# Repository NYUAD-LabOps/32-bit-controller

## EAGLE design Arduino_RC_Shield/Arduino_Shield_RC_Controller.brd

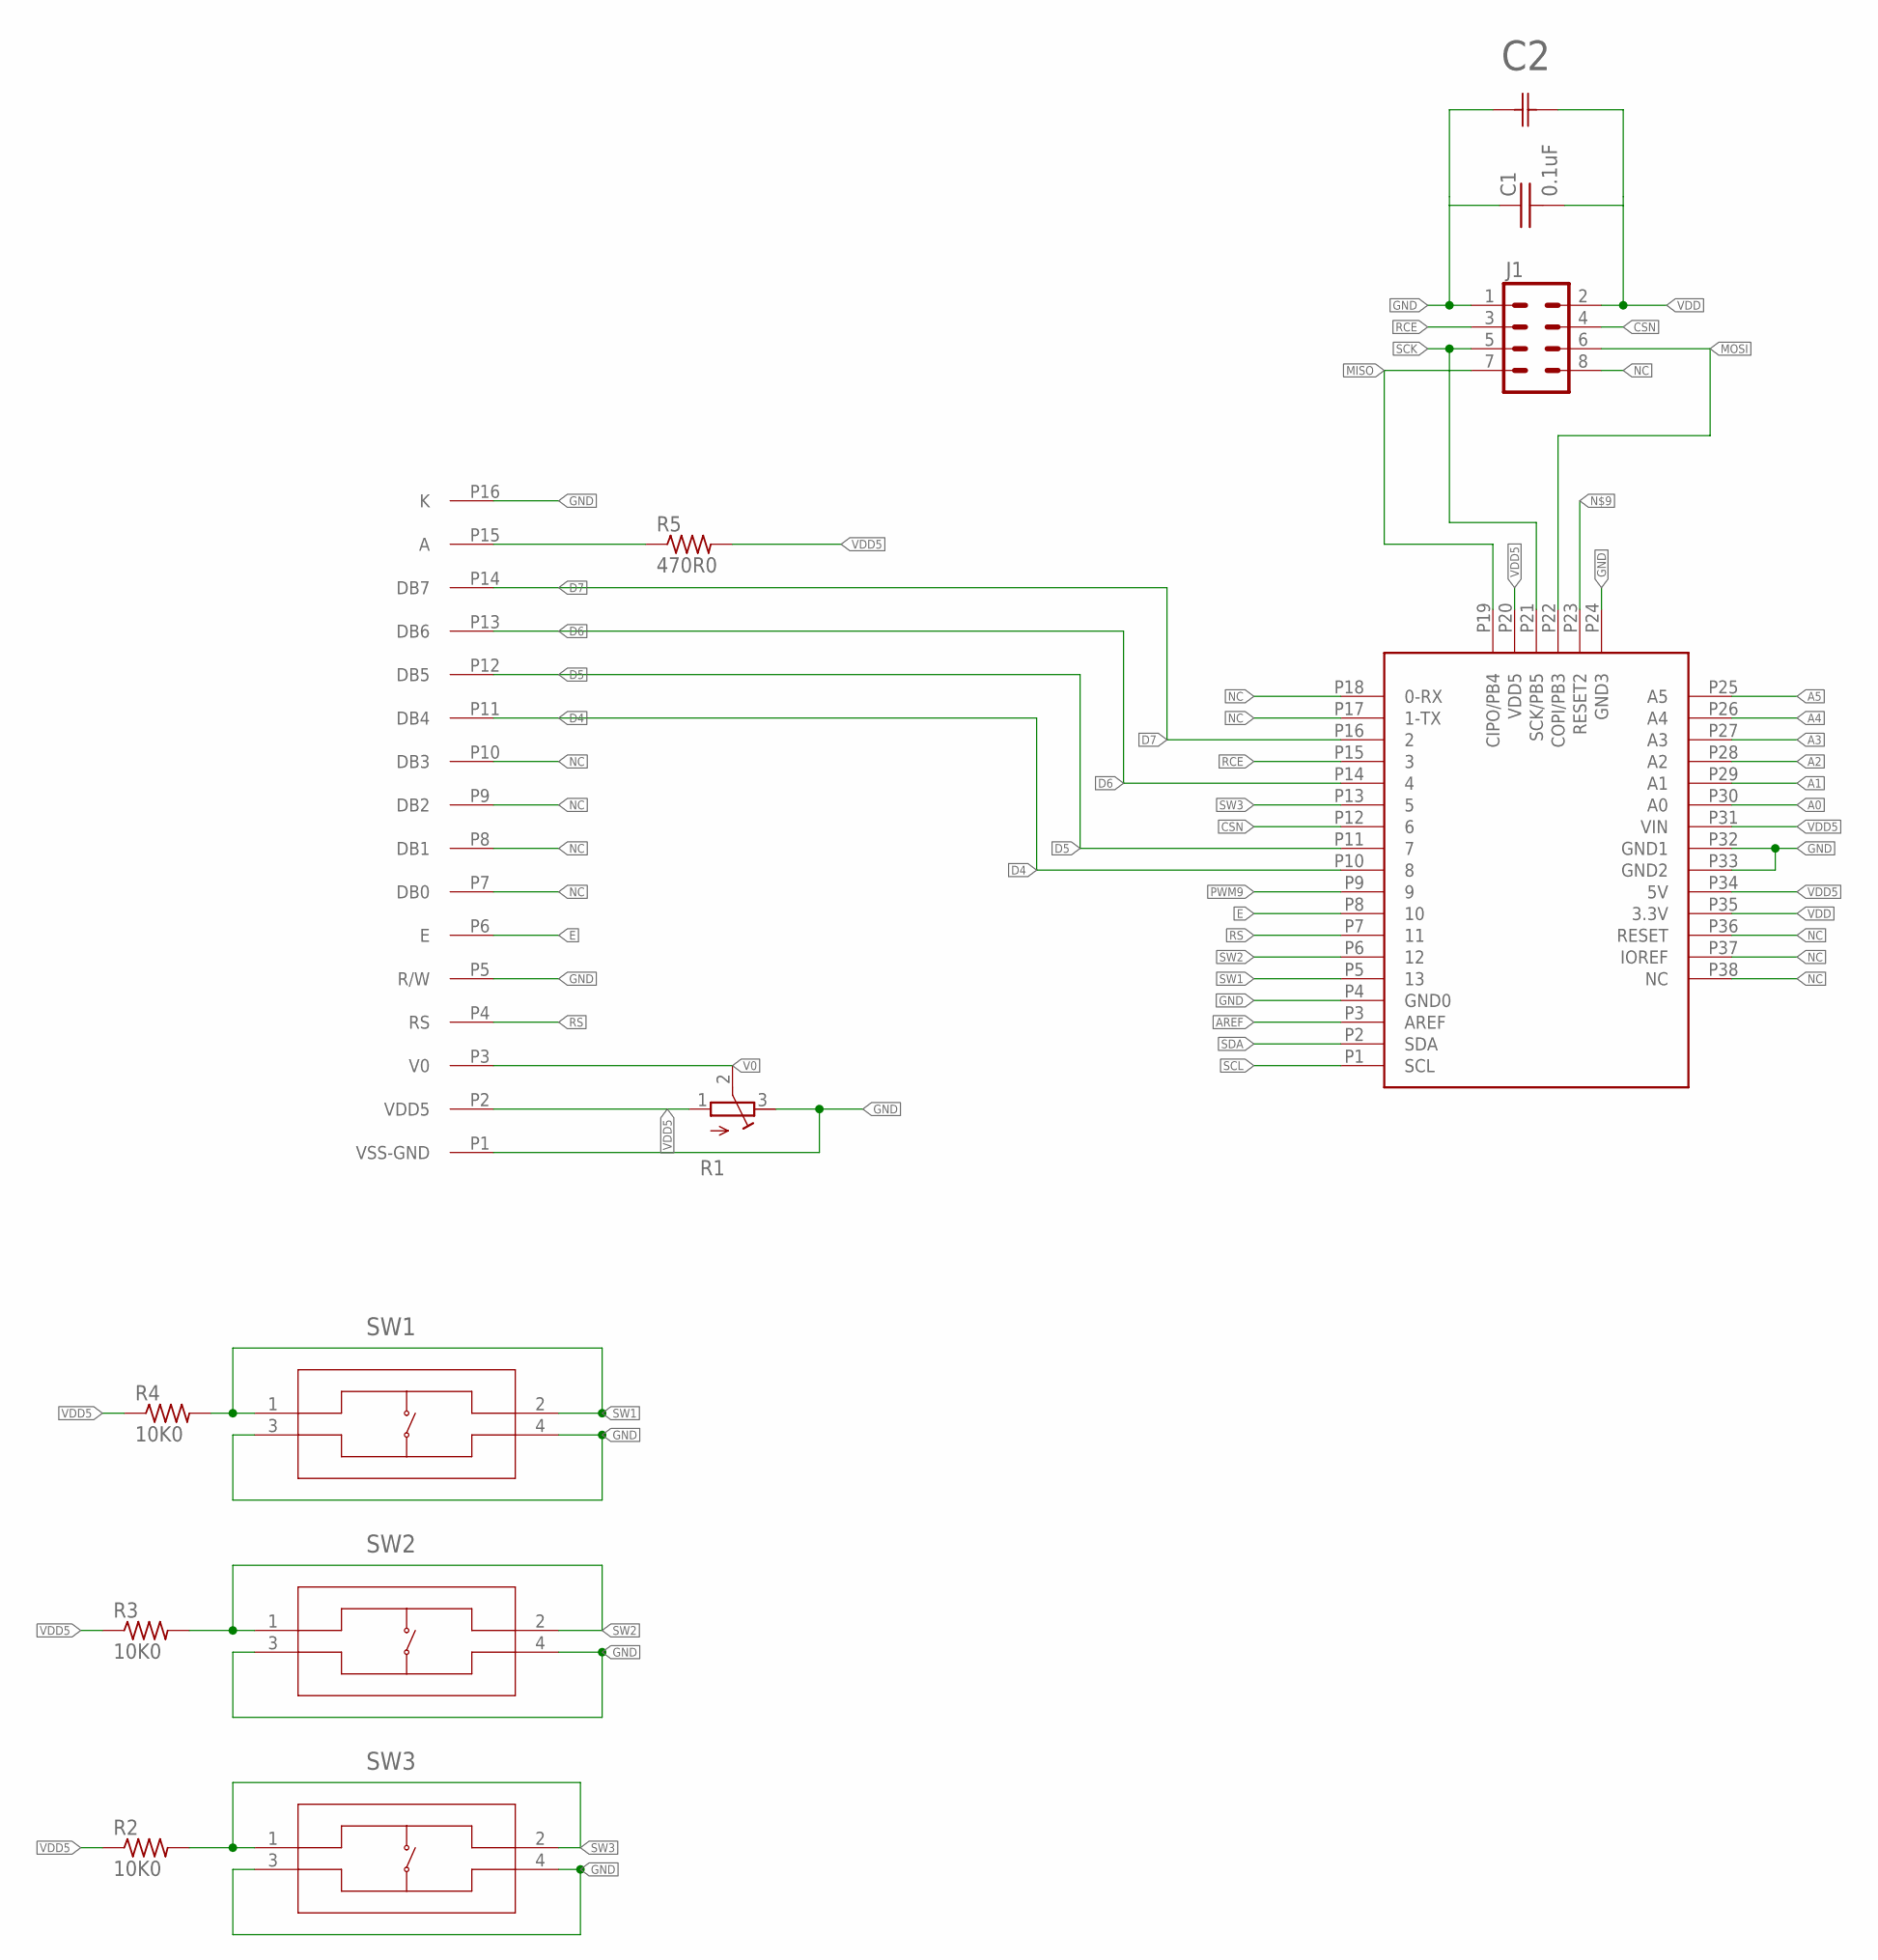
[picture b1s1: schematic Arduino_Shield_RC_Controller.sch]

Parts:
AR1: ARDUINO_R3
C1: 0.1uF; 0402
C2: CAP_470UF_RAD_TH; CAP_YX_10X16_RUB
J1: CONN_04X2; 2X4
LCD1: ADM1602K
R1: R-TRIMM3103; RTRIM3103
R2, R3, R4: 10K0; 0402
R5: 470R0; 0402
SW1, SW2, SW3: PTS810SJG250SMTRLFS; PTS810

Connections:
A0: AR1.P30 (A0)
A1: AR1.P29 (A1)
A2: AR1.P28 (A2)
A3: AR1.P27 (A3)
A4: AR1.P26 (A4)
A5: AR1.P25 (A5)
AREF: AR1.P3 (AREF)
CSN: AR1.P12 (6), J1.4
D4: AR1.P10 (8), LCD1.P11 (DB4)
D5: AR1.P11 (7), LCD1.P12 (DB5)
D6: AR1.P14 (4), LCD1.P13 (DB6)
D7: AR1.P16 (2), LCD1.P14 (DB7)
E: AR1.P8 (10), LCD1.P6 (E)
GND: AR1.P4 (GND0), AR1.P24 (GND3), AR1.P32 (GND1), AR1.P33 (GND2), C1.P$1 (1), C2.1, J1.1, LCD1.P1 (VSS-GND), LCD1.P5 (R/W), LCD1.P16 (K), R1.3 (E), SW1.3, SW1.4, SW2.3, SW2.4, SW3.3, SW3.4
MISO: AR1.P19 (CIPO/PB4), J1.7
MOSI: AR1.P22 (COPI/PB3), J1.6
unnamed: LCD1.P15 (A), R5.P$1 (1)
NC: AR1.P17 (1-TX), AR1.P18 (0-RX), AR1.P36 (RESET), AR1.P37 (IOREF), AR1.P38 (NC), J1.8, LCD1.P7 (DB0), LCD1.P8 (DB1), LCD1.P9 (DB2), LCD1.P10 (DB3)
PWM9: AR1.P9 (9)
RCE: AR1.P15 (3), J1.3
RS: AR1.P7 (11), LCD1.P4 (RS)
SCK: AR1.P21 (SCK/PB5), J1.5
SCL: AR1.P1 (SCL)
SDA: AR1.P2 (SDA)
SW1: AR1.P5 (13), R4.P$2 (2), SW1.1, SW1.2
SW2: AR1.P6 (12), R3.P$2 (2), SW2.1, SW2.2
SW3: AR1.P13 (5), R2.P$2 (2), SW3.1, SW3.2
V0: LCD1.P3 (V0), R1.2 (S)
VDD: AR1.P35 (3.3V), C1.P$2 (2), C2.2, J1.2
VDD5: AR1.P20 (VDD5), AR1.P31 (VIN), AR1.P34 (5V), LCD1.P2 (VDD5), R1.1 (A), R2.P$1 (1), R3.P$1 (1), R4.P$1 (1), R5.P$2 (2)

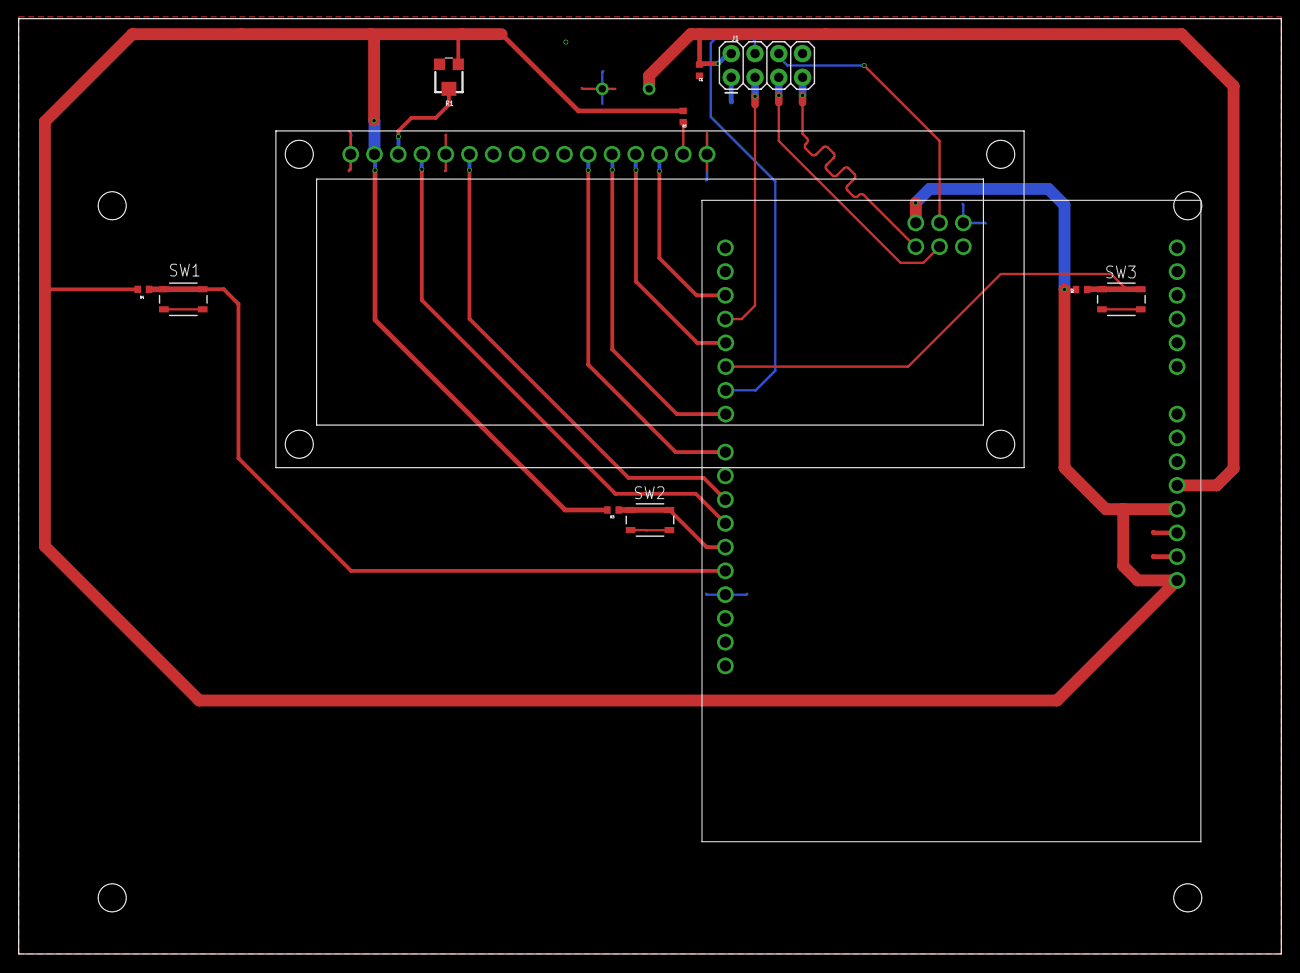
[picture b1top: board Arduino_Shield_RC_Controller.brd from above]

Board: 2 copper layers, 135.0 x 100.0 mm, 13 parts (1 on the bottom side), 20 nets.

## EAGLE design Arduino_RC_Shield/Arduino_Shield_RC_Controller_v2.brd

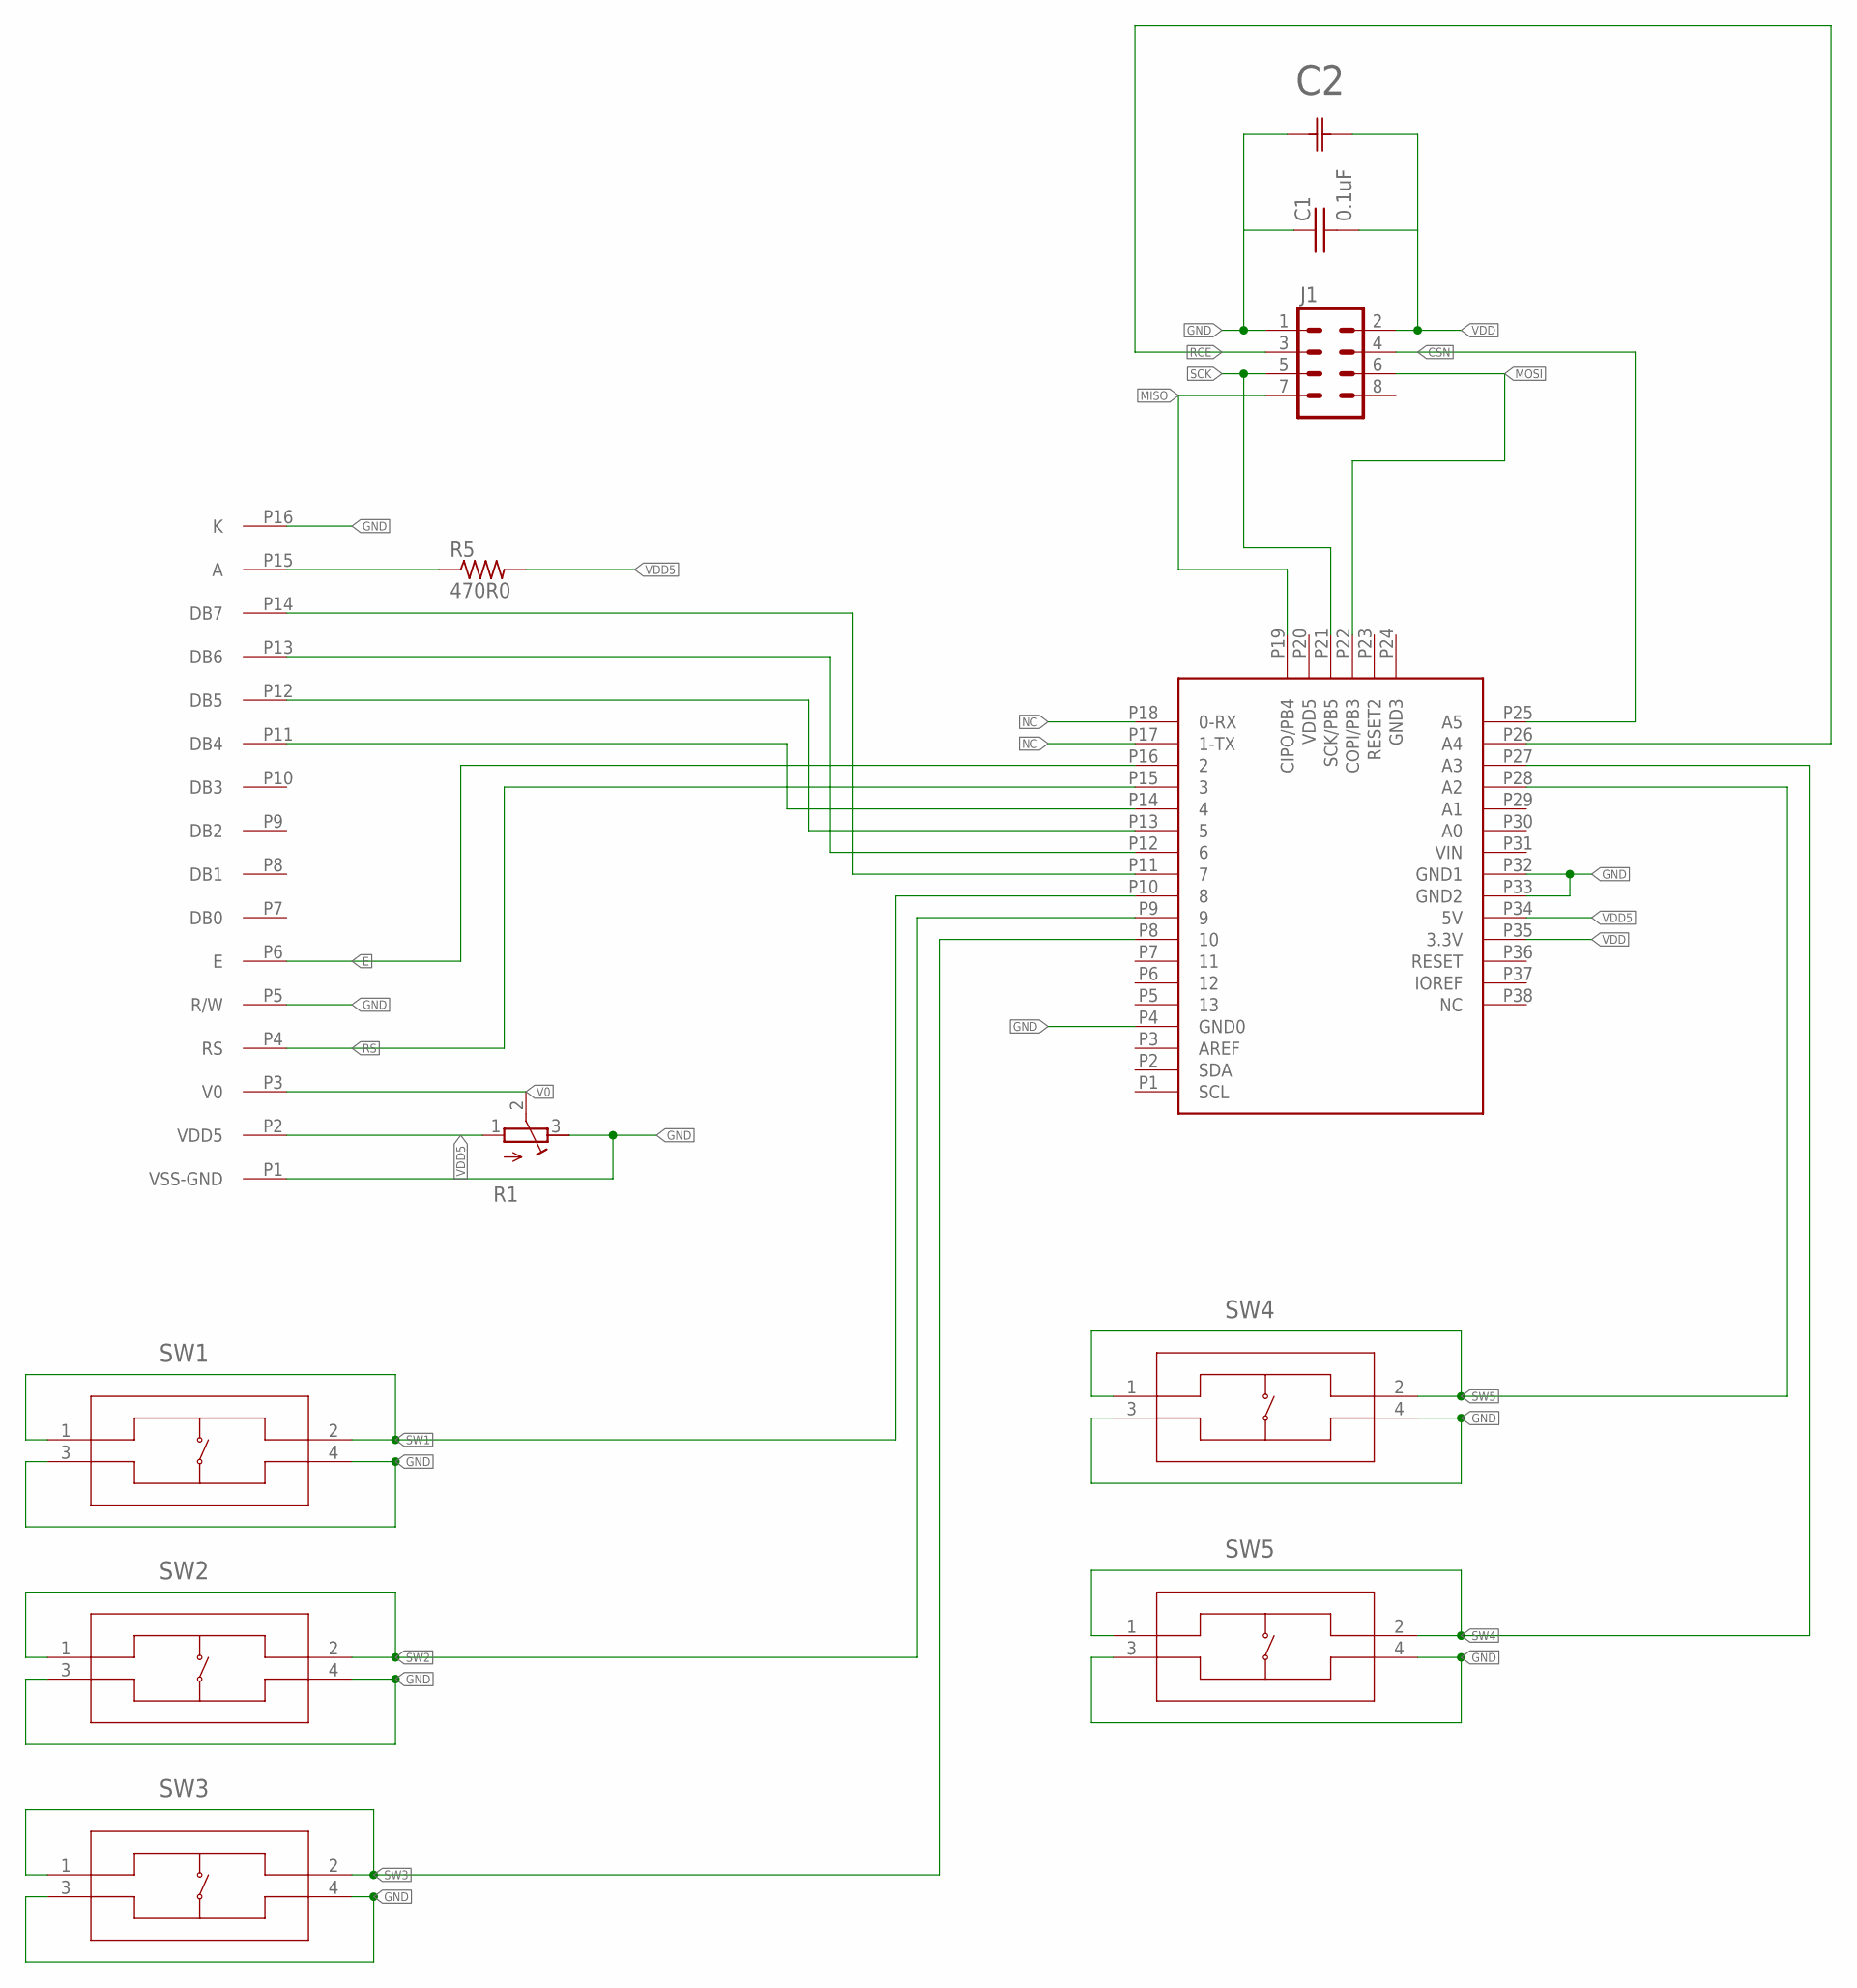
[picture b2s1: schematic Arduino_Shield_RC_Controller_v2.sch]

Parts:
AR1: ARDUINO_R3
C1: 0.1uF; 0402
C2: CAP_470UF_RAD_TH; CAP_YX_10X16_RUB
J1: CONN_04X2; 2X4
LCD1: ADM1602K
R1: R-TRIMM3103; RTRIM3103
R5: 470R0; 0402
SW1, SW2, SW3, SW4, SW5: PTS810SJG250SMTRLFS; PTS810

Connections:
CSN: AR1.P25 (A5), J1.4
E: AR1.P16 (2), LCD1.P6 (E)
GND: AR1.P4 (GND0), AR1.P32 (GND1), AR1.P33 (GND2), C1.P$1 (1), C2.1, J1.1, LCD1.P1 (VSS-GND), LCD1.P5 (R/W), LCD1.P16 (K), R1.3 (E), SW1.3, SW1.4, SW2.3, SW2.4, SW3.3, SW3.4, SW4.3, SW4.4, SW5.3, SW5.4
MISO: AR1.P19 (CIPO/PB4), J1.7
MOSI: AR1.P22 (COPI/PB3), J1.6
unnamed: AR1.P11 (7), LCD1.P14 (DB7)
unnamed: AR1.P12 (6), LCD1.P13 (DB6)
unnamed: AR1.P13 (5), LCD1.P12 (DB5)
unnamed: AR1.P14 (4), LCD1.P11 (DB4)
unnamed: LCD1.P15 (A), R5.P$1 (1)
NC: AR1.P17 (1-TX), AR1.P18 (0-RX)
RCE: AR1.P26 (A4), J1.3
RS: AR1.P15 (3), LCD1.P4 (RS)
SCK: AR1.P21 (SCK/PB5), J1.5
SW1: AR1.P10 (8), SW1.1, SW1.2
SW2: AR1.P9 (9), SW2.1, SW2.2
SW3: AR1.P8 (10), SW3.1, SW3.2
SW4: AR1.P27 (A3), SW5.1, SW5.2
SW5: AR1.P28 (A2), SW4.1, SW4.2
V0: LCD1.P3 (V0), R1.2 (S)
VDD: AR1.P35 (3.3V), C1.P$2 (2), C2.2, J1.2
VDD5: AR1.P34 (5V), LCD1.P2 (VDD5), R1.1 (A), R5.P$2 (2)

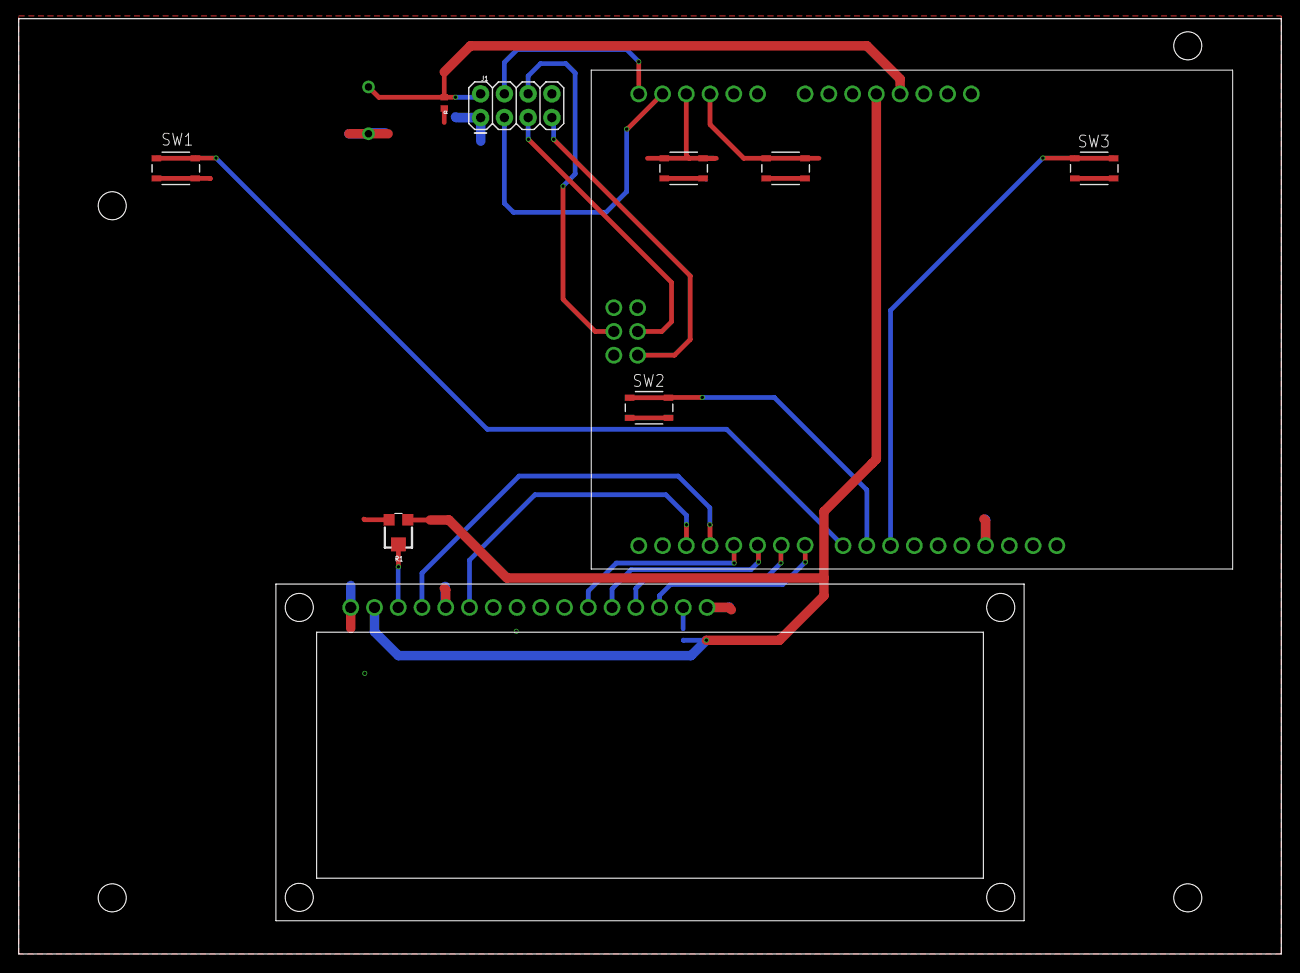
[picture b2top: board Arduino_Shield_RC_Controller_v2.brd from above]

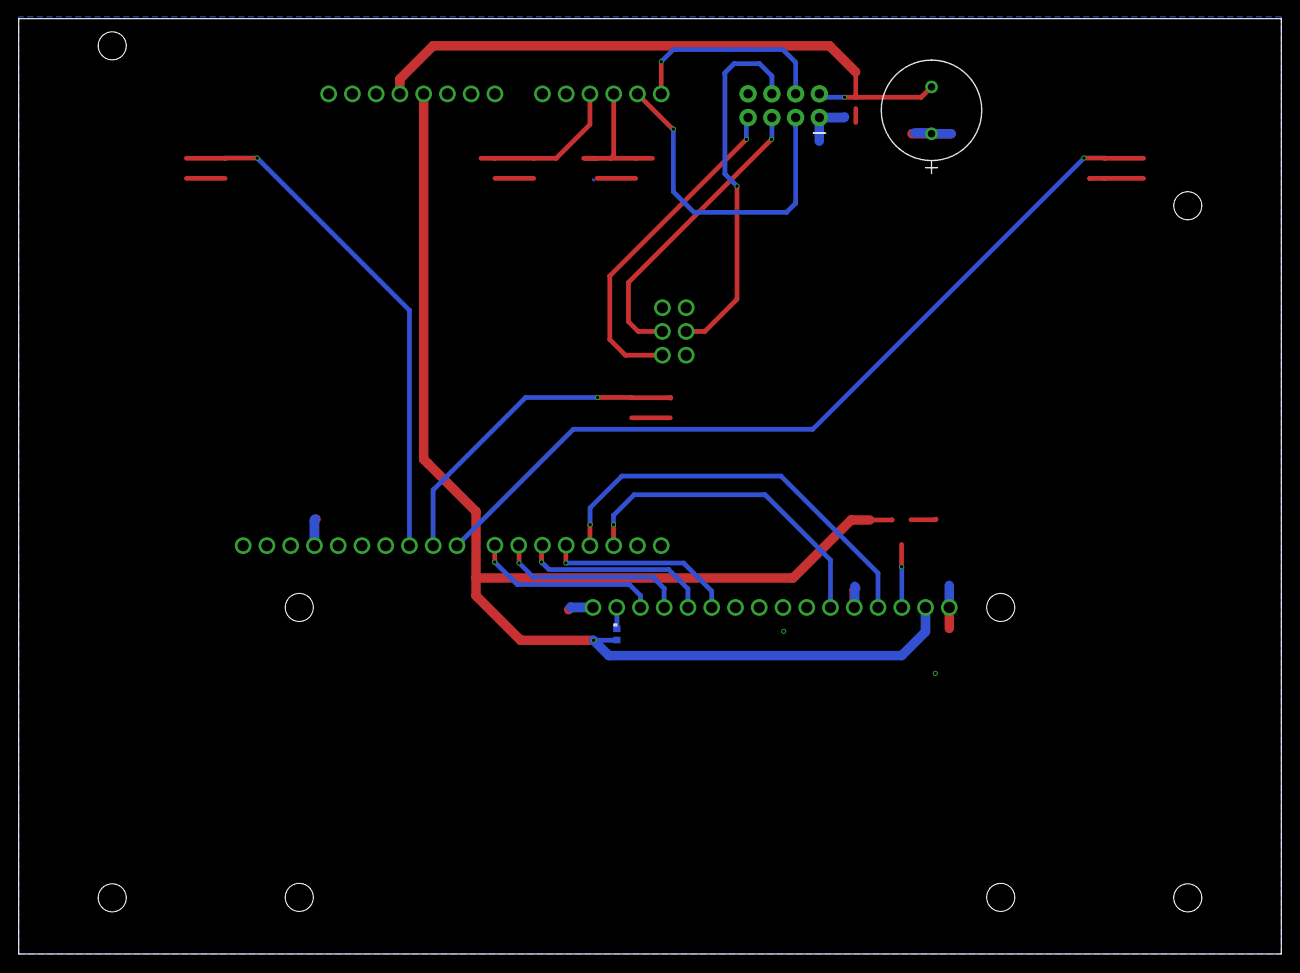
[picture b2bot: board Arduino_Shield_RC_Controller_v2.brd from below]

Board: 2 copper layers, 135.0 x 100.0 mm, 12 parts (2 on the bottom side), 22 nets.

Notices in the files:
parts and their libraries:
COPYRIGHT: Copyright (C) 2018 Accelerated Designs. All rights reserved
COPYRIGHT: Copyright (C) 2023 Ultra Librarian. All rights reserved.
